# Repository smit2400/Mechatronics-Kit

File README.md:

# Mechatronics Kit

Hardware and firmware for an educational robotics kit. A handheld remote controls a hexagonal robot board over **Bluetooth (HC-05)** or **Wi-Fi (ESP-01)**. The repo includes the kit's KiCad designs (a robot controller and two revisions of a motor-driver board), the wireless link firmware, and the sensor tests used for quality checks before shipping.

*Robot controller board — 2-layer, 35 × 54 mm (rendered from the KiCad layout)*

---

## System overview

```
 Remote controller                               Hex robot board
 ┌───────────────────────┐   Bluetooth (HC-05)   ┌───────────────────────┐
 │ Arduino Nano          │ ────────────────────► │ Arduino Nano          │
 │ Joystick (A0/A1)      │         or            │ Motor driver (L293D)  │
 │ HC-05 / ESP-01        │ ────────────────────► │ HC-05 / ESP-01        │
 └───────────────────────┘   Wi-Fi UDP (ESP-01)  │ Sensors               │
                                                 └───────────────────────┘
```

The joystick position is encoded as simple one-byte direction codes and sent over whichever radio is fitted.

## Hardware

**Robot controller** (`hardware/otto-controller/`)
- Built around an Arduino Nano Every, with an L293D dual H-bridge for two DC motors on screw terminals.
- Four servo headers, plus headers for an ultrasonic sensor, two IR sensors, a Bluetooth module and an RFID reader.
- B120 Schottky diode for reverse-polarity protection on the battery input.
- 2-layer, 35 × 54 mm.

**L293D motor-driver breakout** (`hardware/l293d-motor-driver/`)
- An Arduino Nano socket with an L293D driving four outputs (two DC motors), six 3-pin servo/sensor headers, a protected power input and a status LED.
- **Rev 1.0** (May 2022): 47 × 59 mm, Gerbers included.
- **Rev 2:** shrunk to 35 × 54 mm, with fuses added for protection.

| Rev 1.0 | Rev 2 |
|---|---|
|  |  |

## Firmware

**Bluetooth link** (HC-05, master/slave pairing)

| Sketch | Board | Purpose |
|---|---|---|
| `remote-controller/bt_master_at_setup` | Remote | Serial passthrough to configure the HC-05 as master (`AT+ROLE=1`, `AT+CMODE=1`) and read its address |
| `hex-board/bt_slave_at_setup` | Robot | Configures the robot's HC-05 as a slave bound to the master's address |
| `remote-controller/bt_joystick_master` | Remote | Reads the joystick and sends direction codes over Bluetooth |
| `hex-board/bt_slave_receiver` | Robot | Receives direction codes |

**Wi-Fi link** (ESP-01, UDP)

| Sketch | Board | Purpose |
|---|---|---|
| `hex-board/esp01_udp_access_point` | Robot's ESP-01 | Creates a soft access point and listens on UDP port 2000 |
| `remote-controller/esp01_udp_client` | Remote's ESP-01 | Joins the robot's access point and forwards serial bytes as UDP packets |
| `remote-controller/nano_joystick_to_esp01` | Remote's Nano | Reads the joystick and sends commands to the ESP-01 over serial |
| `hex-board/nano_esp01_receiver` | Robot's Nano | Reads commands from the ESP-01 over serial |

Using UDP on a private access point keeps latency low and avoids needing a router. Set your own SSID and password in place of the `YOUR_AP_...` placeholders.

**Sensor tests** (`firmware/sensor-tests/`)
- Bring-up and QC sketches for the HC-SR04 ultrasonic, PIR, IR obstacle and flame sensors, and a button input.
- Several are adapted from standard Arduino and community examples, and keep their original headers.

## Setup procedures

**Pairing the HC-05 modules**
1. Bridge VCC to EN on the remote's HC-05 so it boots into AT mode.
2. Upload `bt_master_at_setup` and send the AT commands listed in the sketch. Note the module's address.
3. Remove the bridge and upload `bt_joystick_master`.
4. Repeat on the robot with `bt_slave_at_setup`, entering the master's address, then upload `bt_slave_receiver`.

**Flashing the ESP-01**
1. Connect the ESP-01 to a USB-TTL adapter.
2. Short GPIO0 to GND to enter flash mode.
3. Start the upload from the Arduino IDE.
4. Press reset as the upload begins.

## Repository structure

```
Mechatronics-Kit/
├── hardware/
│   ├── otto-controller/        Robot controller board (KiCad)
│   └── l293d-motor-driver/     Motor driver, rev 1.0 (+ Gerbers) and rev 2
├── firmware/
│   ├── remote-controller/      Joystick remote: Bluetooth master, ESP-01 client
│   ├── hex-board/              Robot: Bluetooth slave, ESP-01 access point
│   └── sensor-tests/           Sensor bring-up and QC sketches
└── docs/images/                Board renders
```

Open any `.kicad_pro` file in **KiCad 6** or newer. Sketches open in the Arduino IDE; the ESP-01 sketches need the ESP8266 board package.

## Tools

KiCad 6 · Arduino IDE · Arduino Nano / Nano Every · ESP8266 (ESP-01) · HC-05 Bluetooth · L293D

## License

No license is granted. This repository is shared as a portfolio of my work; all rights reserved.

---

**Smit Vaghela** — Embedded Software / Firmware Engineer · [GitHub](https://github.com/smit2400)

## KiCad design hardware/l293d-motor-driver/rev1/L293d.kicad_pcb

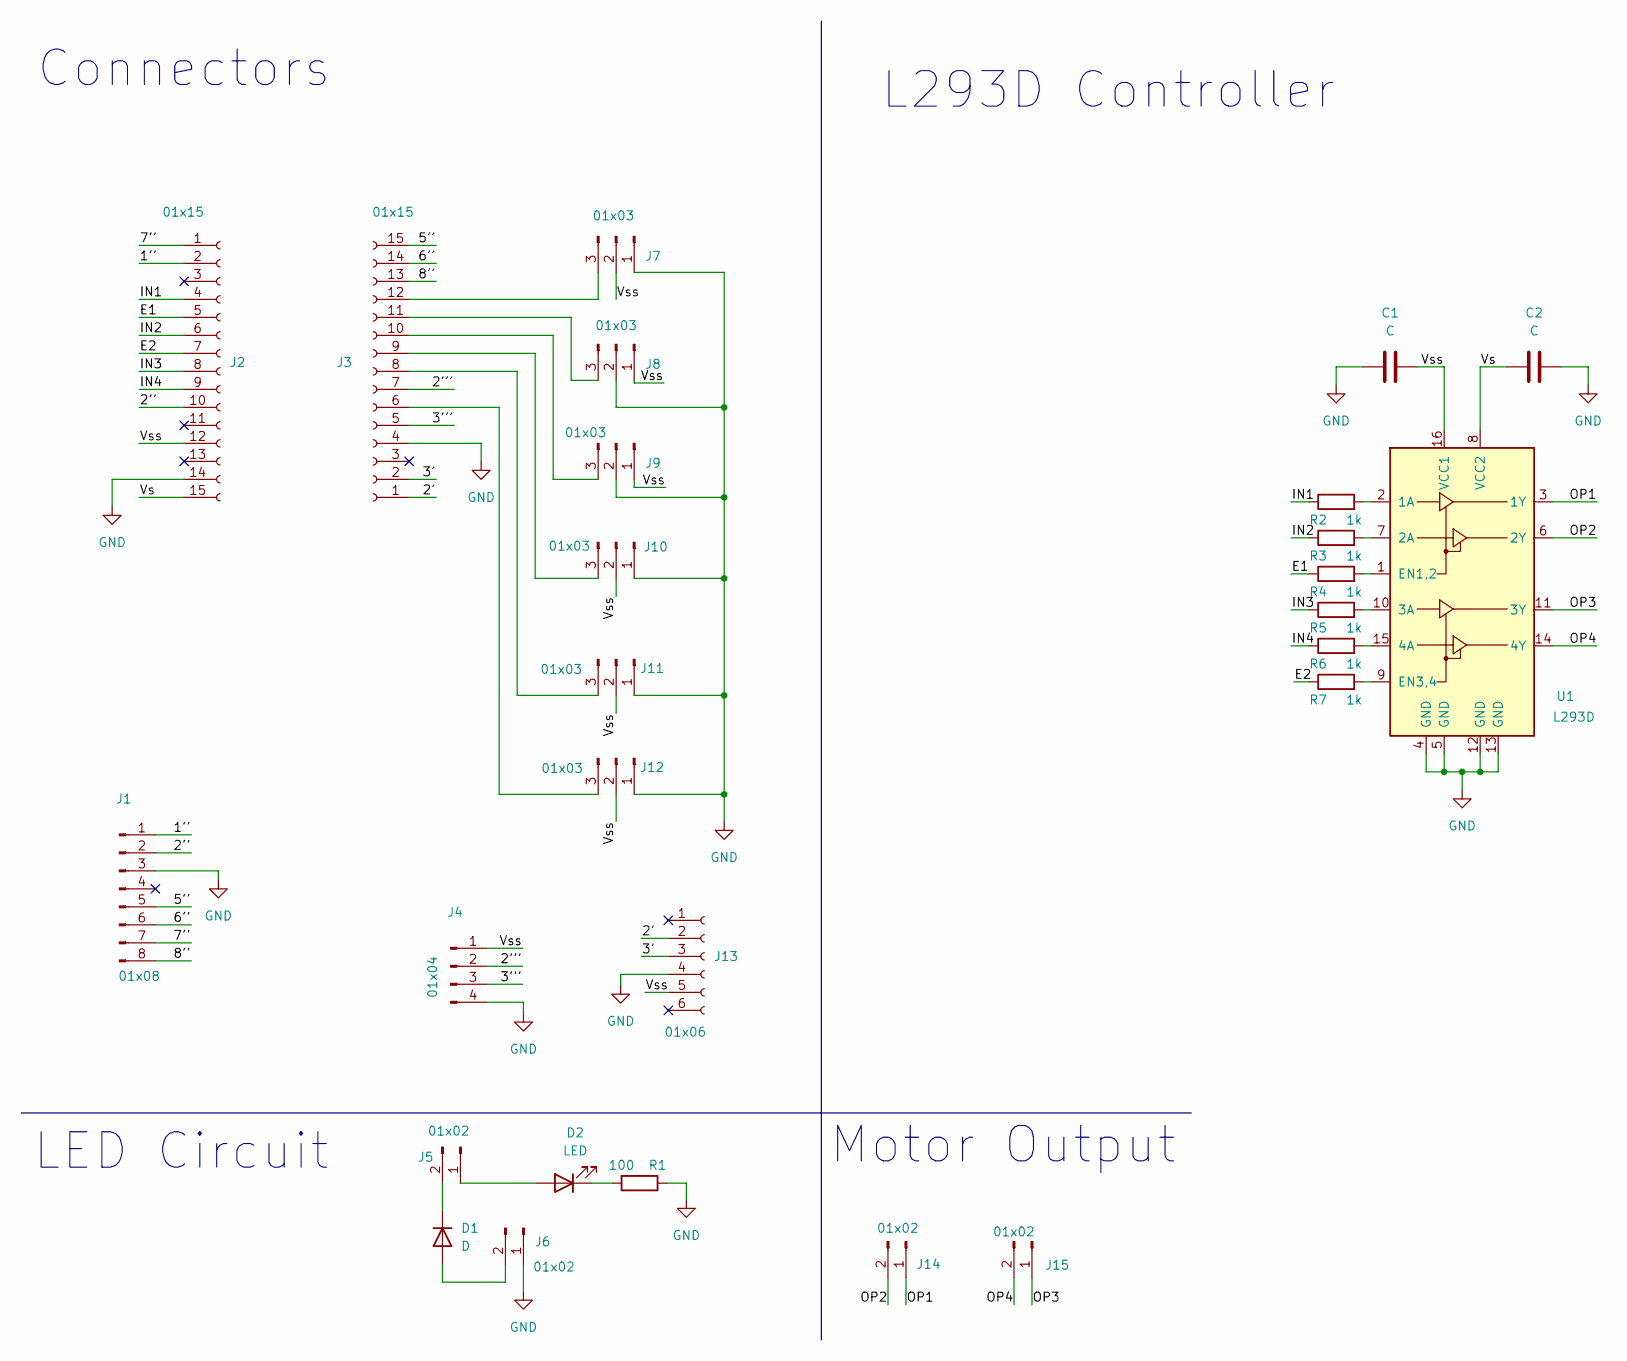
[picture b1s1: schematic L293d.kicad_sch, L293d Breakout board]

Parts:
C1, C2: C; C_0805_2012Metric
D1: D; D_SMA
D2: LED; LED_1206_3216Metric
J1: 01x08; PinHeader_1x08_P2.54mm_Vertical
J2, J3: 01x15; PinHeader_1x15_P2.54mm_Vertical
J4: 01x04; PinHeader_1x04_P2.54mm_Vertical
J5: 01x02; PinHeader_1x02_P2.54mm_Vertical
J6: 01x02; JST_EH_B2B-EH-A_1x02_P2.50mm_Vertical
J7, J8, J9, J10, J11, J12: 01x03; PinHeader_1x03_P2.54mm_Vertical
J13: 01x06; PinHeader_1x06_P2.54mm_Vertical
J14, J15: 01x02; JWT_A3963_1x02_P3.96mm_Vertical
R1: 100; R_0805_2012Metric
R2, R3, R4, R5, R6, R7: 1k; R_0805_2012Metric
U1: L293D; DIP-16_W7.62mm

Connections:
/1'': J1.1, J2.2
/2': J3.1, J13.2
/2'': J1.2, J2.10
/2''': J3.7, J4.2
/3': J3.2, J13.3
/3''': J3.5, J4.3
/5'': J1.5, J3.15
/6'': J1.6, J3.14
/7'': J1.7, J2.1
/8'': J1.8, J3.13
/E1: J2.5, R4.1
/E2: J2.7, R7.1
/IN1: J2.4, R2.1
/IN2: J2.6, R3.1
/IN3: J2.8, R5.1
/IN4: J2.9, R6.1
/OP1: J14.1, U1.3 (1Y)
/OP2: J14.2, U1.6 (2Y)
/OP3: J15.1, U1.11 (3Y)
/OP4: J15.2, U1.14 (4Y)
/Vs: C2.1, J2.15, U1.8 (VCC2)
/Vss: C1.1, J2.12, J4.1, J7.2, J8.1, J9.1, J10.2, J11.2, J12.2, J13.5, U1.16 (VCC1)
GND: C1.2, C2.2, J1.3, J2.14, J3.4, J4.4, J6.1, J7.1, J8.2, J9.2, J10.1, J11.1, J12.1, J13.4, R1.1, U1.4 (GND), U1.5 (GND), U1.12 (GND), U1.13 (GND)
unnamed: D1.1 (K), J5.2
unnamed: D1.2 (A), J6.2
unnamed: D2.1 (K), R1.2
unnamed: D2.2 (A), J5.1
unnamed: J3.10, J9.3
unnamed: J3.11, J8.3
unnamed: J3.12, J7.3
unnamed: J3.9, J10.3
unnamed: J3.8, J11.3
unnamed: J3.6, J12.3
unnamed: R2.2, U1.2 (1A)
unnamed: R3.2, U1.7 (2A)
unnamed: R4.2, U1.1 (EN1,2)
unnamed: R5.2, U1.10 (3A)
unnamed: R6.2, U1.15 (4A)
unnamed: R7.2, U1.9 (EN3,4)

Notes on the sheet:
Motor Output
L293D Controller
Connectors
LED Circuit

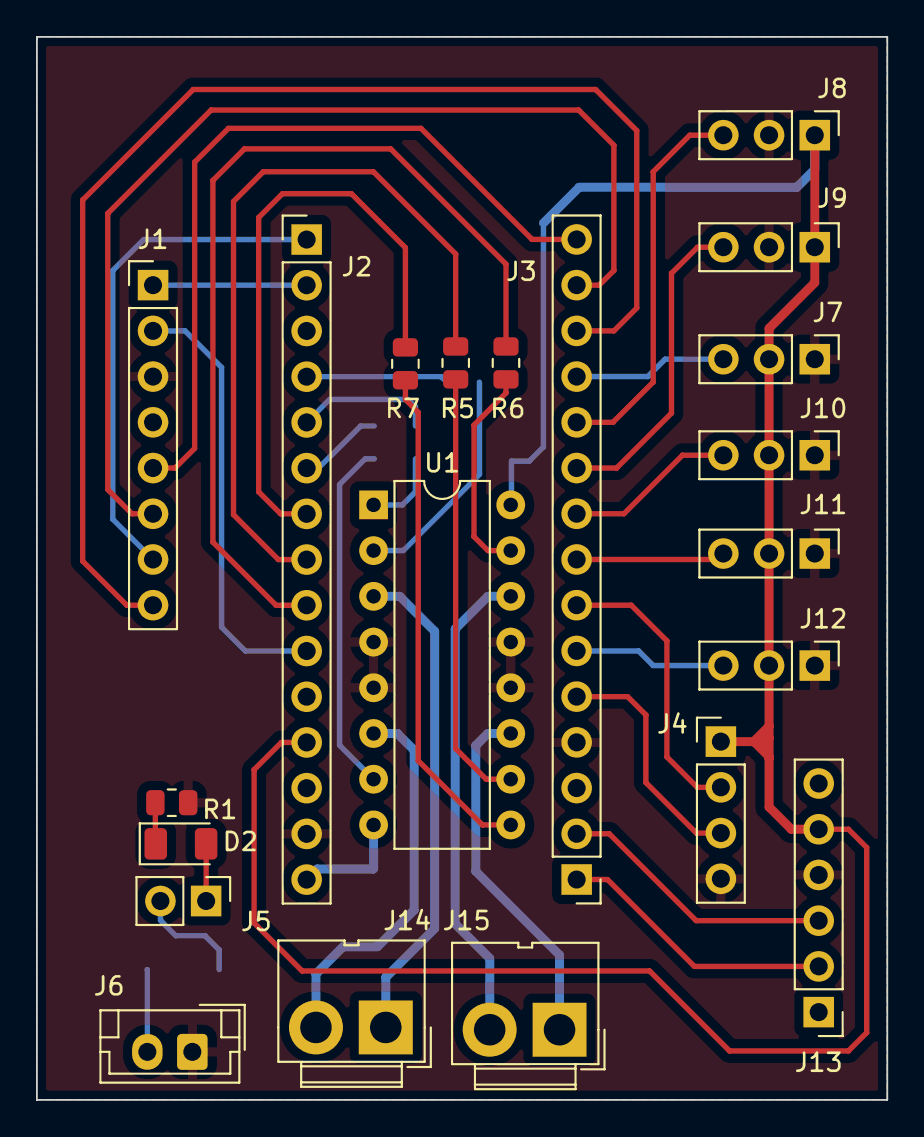
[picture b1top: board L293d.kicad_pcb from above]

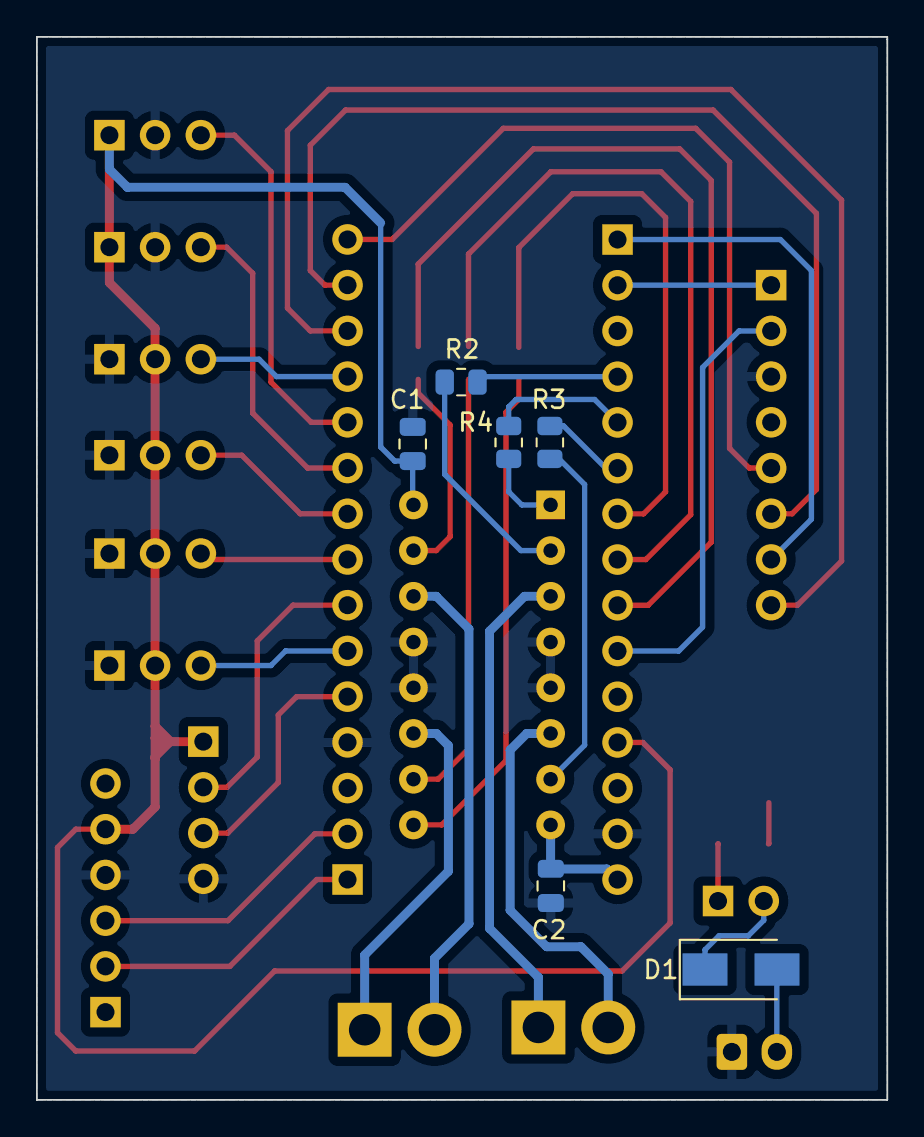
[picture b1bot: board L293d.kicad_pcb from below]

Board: 2 copper layers, 47.2 x 59.1 mm, 27 parts (6 on the bottom side), 39 nets.

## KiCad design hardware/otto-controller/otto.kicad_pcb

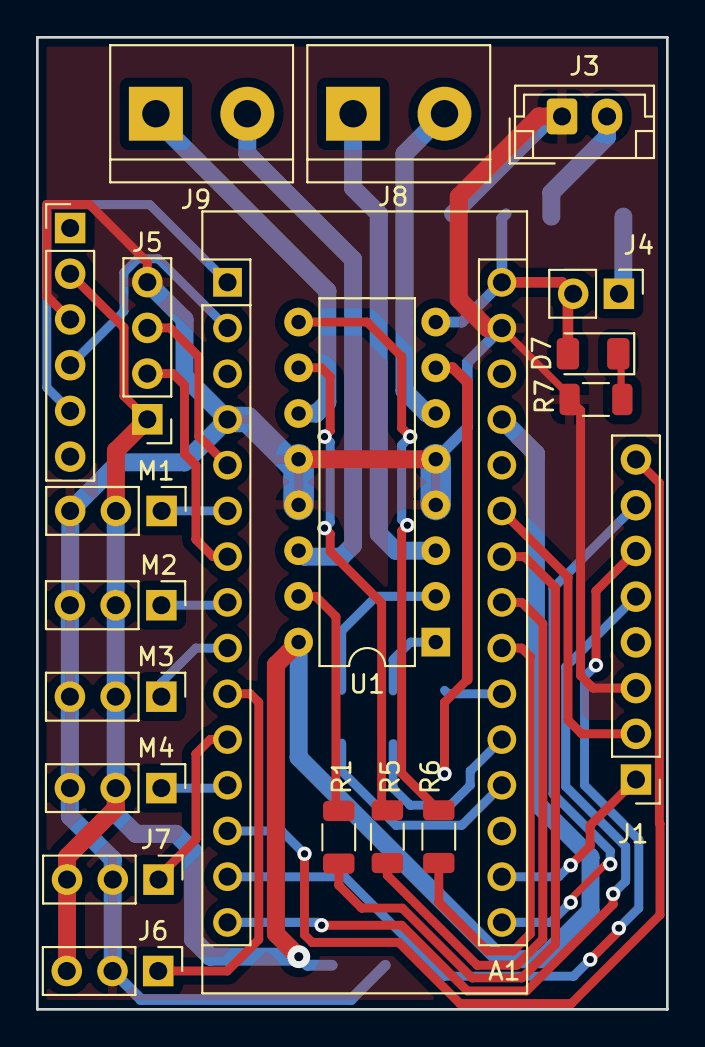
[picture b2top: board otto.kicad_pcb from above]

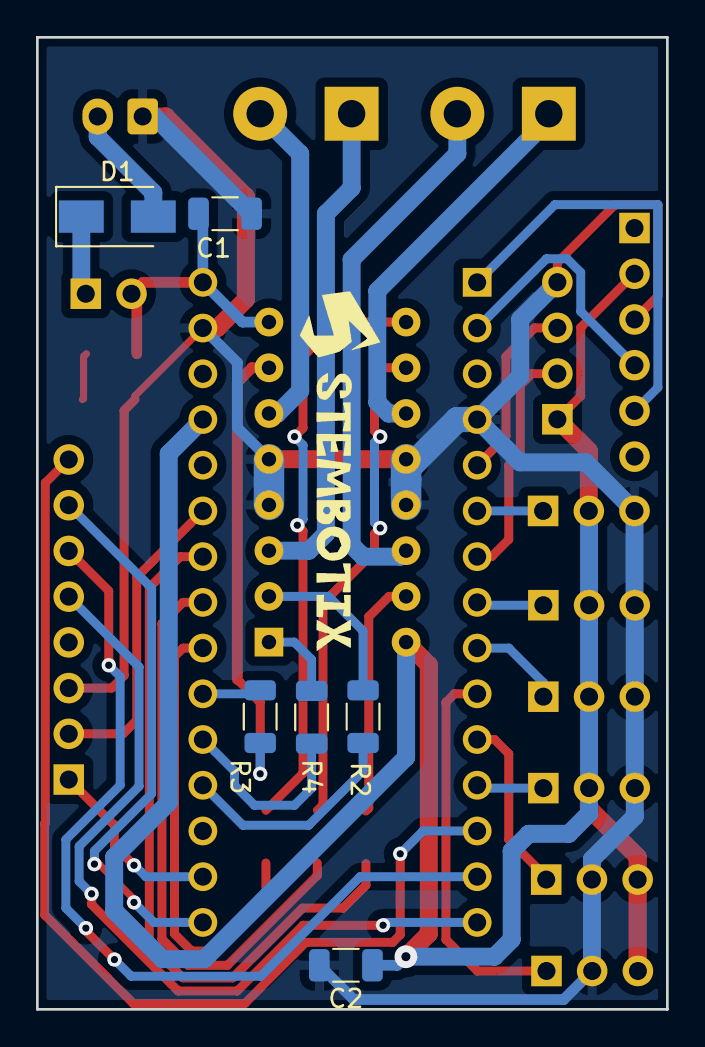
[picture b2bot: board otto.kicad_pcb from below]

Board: 2 copper layers, 35.0 x 54.0 mm, 25 parts (6 on the bottom side), 36 nets.

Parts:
A1: Arduino_Nano_Every; Arduino_Nano
C1, C2: 100uF; C_1206_3216Metric
D1: M7; D_SMA
D7: LED; LED_1206_3216Metric
J1: RFID_module; PinHeader_1x08_P2.54mm_Vertical
J3: Battery; JST_EH_B2B-EH-A_1x02_P2.50mm_Vertical
J4: POWER; PinHeader_1x02_P2.54mm_Vertical
J5: Ultrasonic; PinHeader_1x04_P2.54mm_Vertical
J6: IR1; PinHeader_1x03_P2.54mm_Vertical
J7: IR2; PinHeader_1x03_P2.54mm_Vertical
J8: Motor1; TerminalBlock_bornier-2_P5.08mm
J9: Motor2; TerminalBlock_bornier-2_P5.08mm
M1: Servo1; PinHeader_1x03_P2.54mm_Vertical
M2: Servo2; PinHeader_1x03_P2.54mm_Vertical
M3: Servo3; PinHeader_1x03_P2.54mm_Vertical
M4: Servo4; PinHeader_1x03_P2.54mm_Vertical
R1, R2, R3, R4, R5, R6, R7: R; R_1206_3216Metric
U1: L293D; DIP-16_W7.62mm

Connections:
/1A: A1.19 (A0), R2.2
/2A: A1.21 (A2), R3.2
/3A: A1.23 (SDA/A4), R5.2
/4A: A1.24 (SCL/A5), R1.2
/CS_RFID: A1.13 (D10), J1.8
/ECHO: A1.5 (D2), J5.3
/EN12: A1.20 (A1), R4.2
/EN34: A1.22 (A3), R6.2
/IR1: A1.10 (D7), J6.1
/IR2: A1.11 (D8), J7.1
/MISO: A1.15 (MISO), J1.5
/MOSI: A1.14 (MOSI), J1.6
/RST_RFID: A1.25 (A6), J1.2
/SCK: A1.16 (SCK), J1.7
/SERVO1: A1.6 (D3), M1.1 (PWM)
/SERVO2: A1.8 (D5), M2.1 (PWM)
/SERVO3: A1.9 (D6), M3.1 (PWM)
/SERVO4: A1.12 (D9), M4.1 (PWM)
/TRIG: A1.7 (D4), J5.2
/V3.3: A1.17 (3V3), J1.1
/VIN: A1.30 (VIN), C1.1, D7.2 (A), J4.2, U1.8 (VCC2)
GNDREF: A1.4 (GND), A1.29 (GND), C1.2, C2.2, J1.3, J3.1, J5.4, J6.2, J7.2, M1.3 (-), M2.3 (-), M3.3 (-), M4.3 (-), R7.1, U1.4 (GND), U1.5 (GND), U1.12 (GND), U1.13 (GND)
unnamed: D1.1 (K), J4.1
unnamed: D1.2 (A), J3.2
unnamed: D7.1 (K), R7.2
unnamed: J8.1, U1.3 (1Y)
unnamed: J8.2, U1.6 (2Y)
unnamed: J9.1, U1.11 (3Y)
unnamed: J9.2, U1.14 (4Y)
unnamed: R1.1, U1.15 (4A)
unnamed: R2.1, U1.2 (1A)
unnamed: R3.1, U1.7 (2A)
unnamed: R4.1, U1.1 (EN1,2)
unnamed: R5.1, U1.10 (3A)
unnamed: R6.1, U1.9 (EN3,4)
VCC: A1.27 (+5V), C2.1, J5.1, J6.3, J7.3, M1.2 (+), M2.2 (+), M3.2 (+), M4.2 (+), U1.16 (VCC1)
